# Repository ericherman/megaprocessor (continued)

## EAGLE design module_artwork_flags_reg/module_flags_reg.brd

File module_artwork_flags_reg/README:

Status Register

The status register is a collection of bits that record various aspects
of the results of previous calculations. Whilst PS is internally a 16
bit register only 8 bit are visible to the user, the other hidden 8 bits
are used during complex operations such as multiplication etc. and do
not convey any information from one instruction to the next.

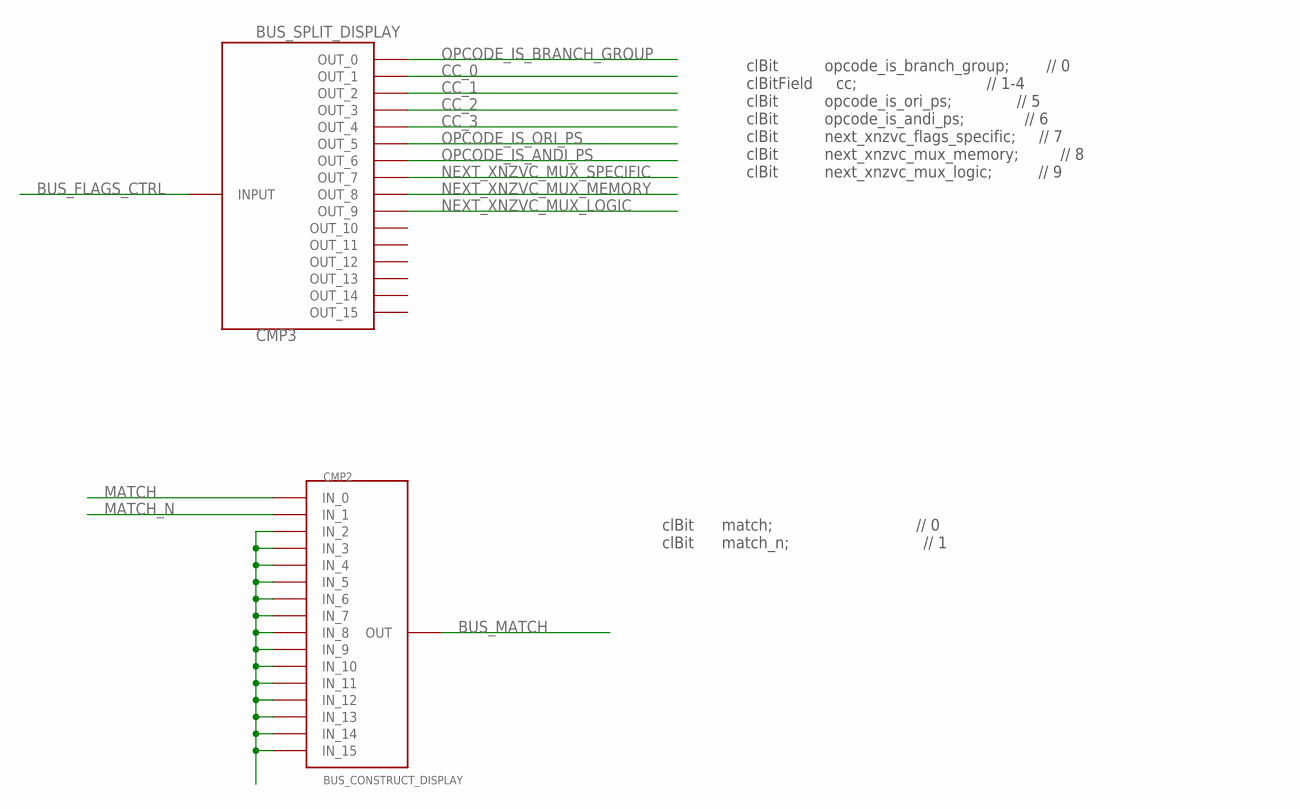
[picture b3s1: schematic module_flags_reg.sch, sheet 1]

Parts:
CMP2: BUS_CONSTRUCT_DISPLAY; BUS_SPLIT_DISPLAY
CMP3: BUS_SPLIT_DISPLAY

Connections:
BUS_FLAGS_CTRL: CMP3.INPUT
BUS_MATCH: CMP2.INPUT (OUT)
CC_0: CMP3.P$2 (OUT_1); also elsewhere on the board
CC_1: CMP3.P$3 (OUT_2); also elsewhere on the board
CC_2: CMP3.P$4 (OUT_3); also elsewhere on the board
CC_3: CMP3.P$5 (OUT_4); also elsewhere on the board
MATCH: CMP2.P$1 (IN_0); also elsewhere on the board
MATCH_N: CMP2.P$2 (IN_1); also elsewhere on the board
unnamed: CMP2.P$3 (IN_2), CMP2.P$4 (IN_3), CMP2.P$5 (IN_4), CMP2.P$6 (IN_5), CMP2.P$7 (IN_6), CMP2.P$8 (IN_7), CMP2.P$9 (IN_8), CMP2.P$10 (IN_9), CMP2.P$11 (IN_10), CMP2.P$12 (IN_11), CMP2.P$13 (IN_12), CMP2.P$14 (IN_13), CMP2.P$15 (IN_14), CMP2.P$16 (IN_15)
NEXT_XNZVC_MUX_LOGIC: CMP3.P$10 (OUT_9); also elsewhere on the board
NEXT_XNZVC_MUX_MEMORY: CMP3.P$9 (OUT_8); also elsewhere on the board
NEXT_XNZVC_MUX_SPECIFIC: CMP3.P$8 (OUT_7); also elsewhere on the board
OPCODE_IS_ANDI_PS: CMP3.P$7 (OUT_6); also elsewhere on the board
OPCODE_IS_BRANCH_GROUP: CMP3.P$1 (OUT_0); also elsewhere on the board
OPCODE_IS_ORI_PS: CMP3.P$6 (OUT_5); also elsewhere on the board

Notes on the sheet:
clBit opcode_is_branch_group; // 0 clBitField cc; // 1-4 clBit opcode_is_ori_ps; // 5 clBit opcode_is_andi_ps; // 6 clBit next_xnzvc_flags_specific; // 7 clBit next_xnzvc_mux_memory; // 8 clBit next_xnzvc_mux_logic; // 9
clBit match; // 0 clBit match_n; // 1

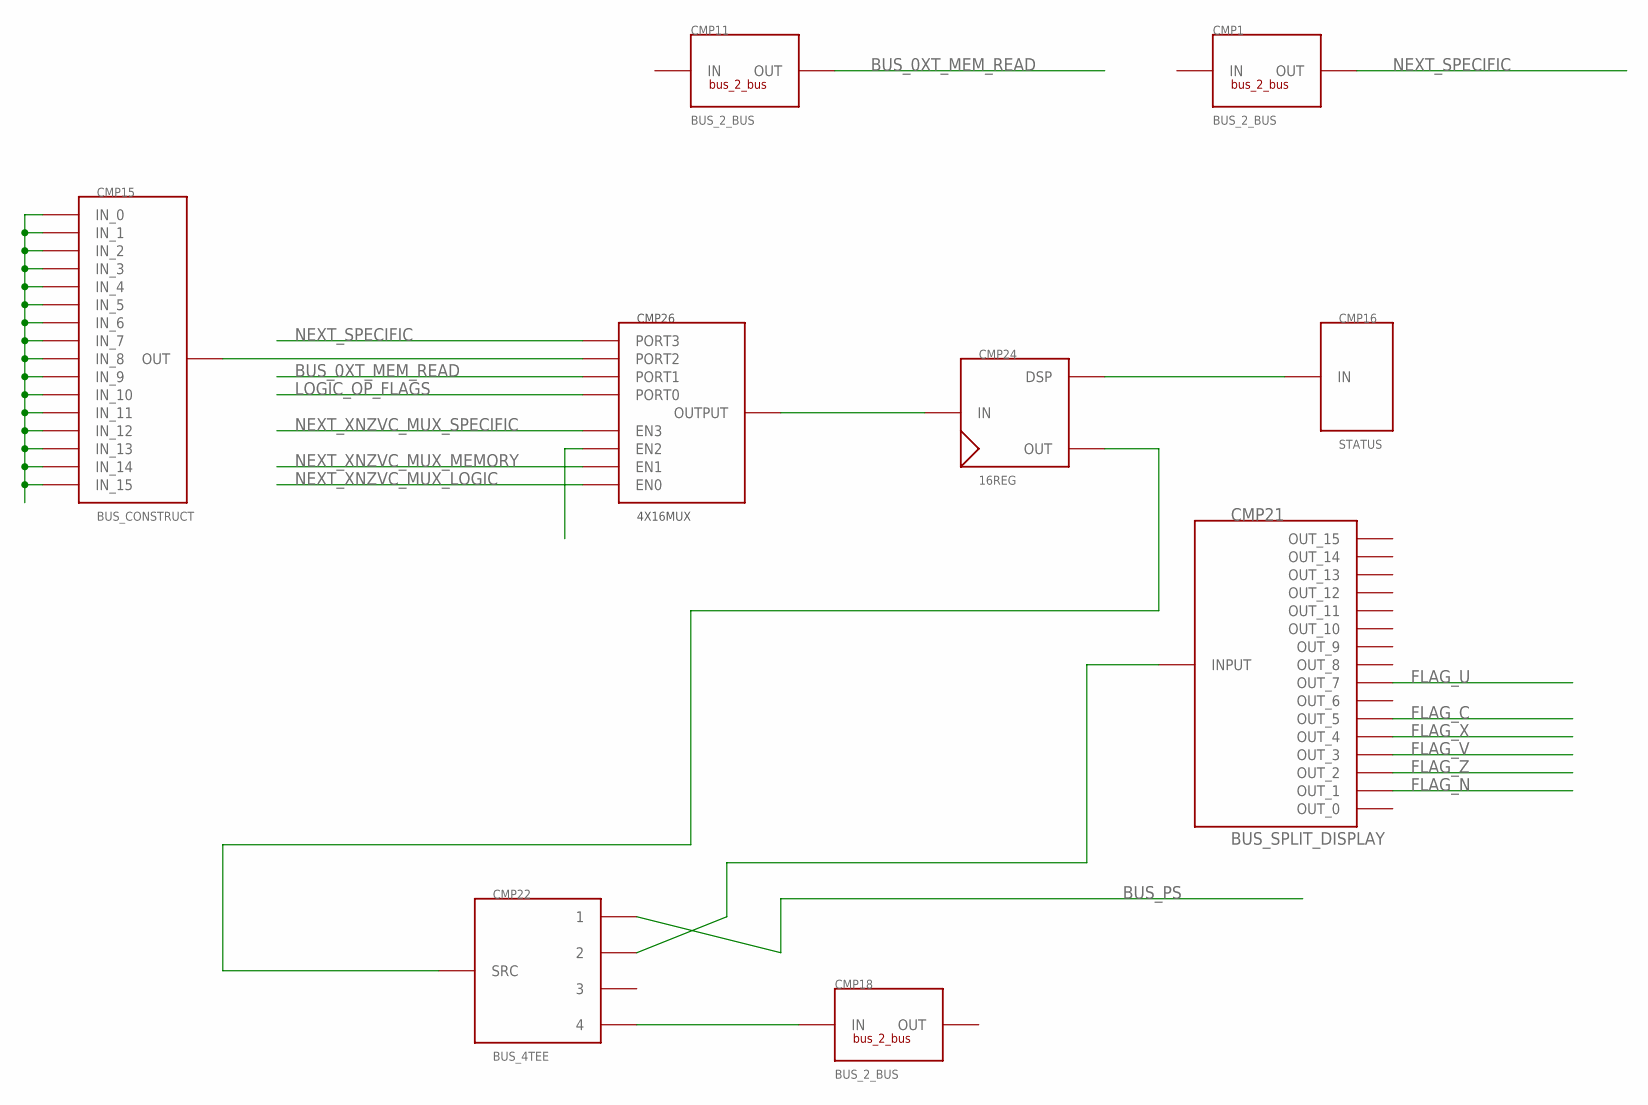
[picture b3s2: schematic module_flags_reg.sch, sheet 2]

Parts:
CMP1, CMP11, CMP18: BUS_2_BUS; BUS2BUS
CMP15: BUS_CONSTRUCT; BUS_SPLIT
CMP16: STATUS
CMP21: BUS_SPLIT_DISPLAY
CMP22: BUS_4TEE
CMP24: 16REG
CMP26: 4X16MUX

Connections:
BUS_0XT_MEM_READ: CMP11.P$2 (OUT), CMP26.PORT1
BUS_PS: CMP22.1; also elsewhere on the board
FLAG_C: CMP21.P$6 (OUT_5); also elsewhere on the board
FLAG_N: CMP21.P$2 (OUT_1); also elsewhere on the board
FLAG_U: CMP21.P$8 (OUT_7); also elsewhere on the board
FLAG_V: CMP21.P$4 (OUT_3); also elsewhere on the board
FLAG_X: CMP21.P$5 (OUT_4)
FLAG_Z: CMP21.P$3 (OUT_2); also elsewhere on the board
LOGIC_OP_FLAGS: CMP26.PORT0; also elsewhere on the board
unnamed: CMP16.P$1, CMP24.DISPLAY (DSP)
unnamed: CMP22.SRC, CMP24.OUT
unnamed: CMP18.P$1 (IN), CMP22.4
unnamed: CMP15.INPUT (OUT), CMP26.PORT2
unnamed: CMP24.INPUT (IN), CMP26.PORTOUT (OUTPUT)
unnamed: CMP15.P$1 (IN_0), CMP15.P$2 (IN_1), CMP15.P$3 (IN_2), CMP15.P$4 (IN_3), CMP15.P$5 (IN_4), CMP15.P$6 (IN_5), CMP15.P$7 (IN_6), CMP15.P$8 (IN_7), CMP15.P$9 (IN_8), CMP15.P$10 (IN_9), CMP15.P$11 (IN_10), CMP15.P$12 (IN_11), CMP15.P$13 (IN_12), CMP15.P$14 (IN_13), CMP15.P$15 (IN_14), CMP15.P$16 (IN_15)
unnamed: CMP21.INPUT, CMP22.2
NEXT_SPECIFIC: CMP1.P$2 (OUT), CMP26.PORT3
NEXT_XNZVC_MUX_LOGIC: CMP26.EN0; also elsewhere on the board
NEXT_XNZVC_MUX_MEMORY: CMP26.EN1; also elsewhere on the board
NEXT_XNZVC_MUX_SPECIFIC: CMP26.EN3; also elsewhere on the board

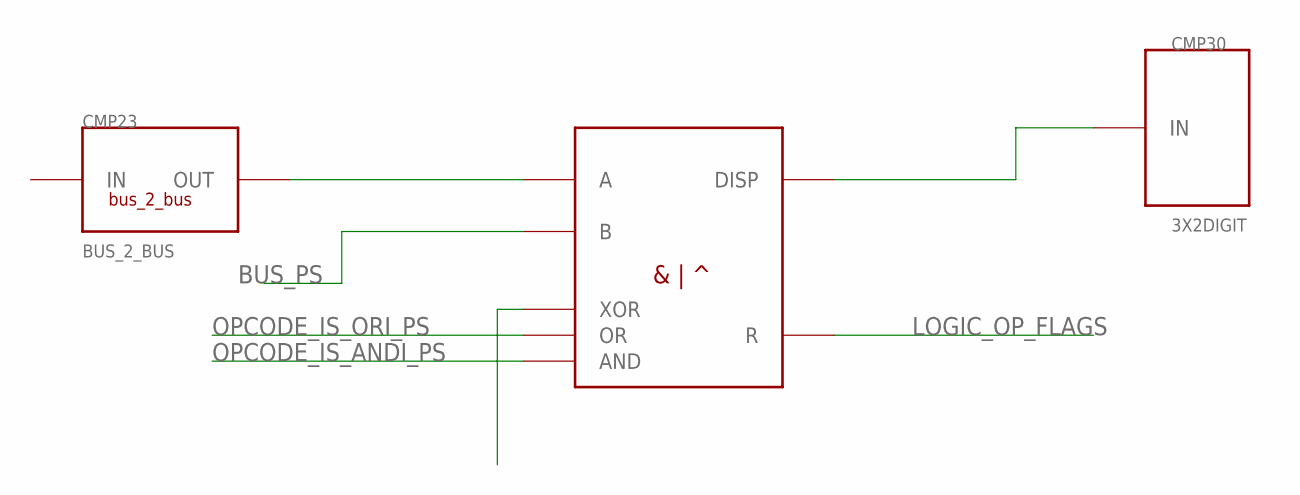
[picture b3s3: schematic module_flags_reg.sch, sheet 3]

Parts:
CMP23: BUS_2_BUS; BUS2BUS
CMP28: 8BIT_LOGIC
CMP30: 3X2DIGIT

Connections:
BUS_PS: CMP28.B; also elsewhere on the board
LOGIC_OP_FLAGS: CMP28.R; also elsewhere on the board
unnamed: CMP28.DISP, CMP30.P$1
unnamed: CMP23.P$2 (OUT), CMP28.A
OPCODE_IS_ANDI_PS: CMP28.AND; also elsewhere on the board
OPCODE_IS_ORI_PS: CMP28.OR; also elsewhere on the board

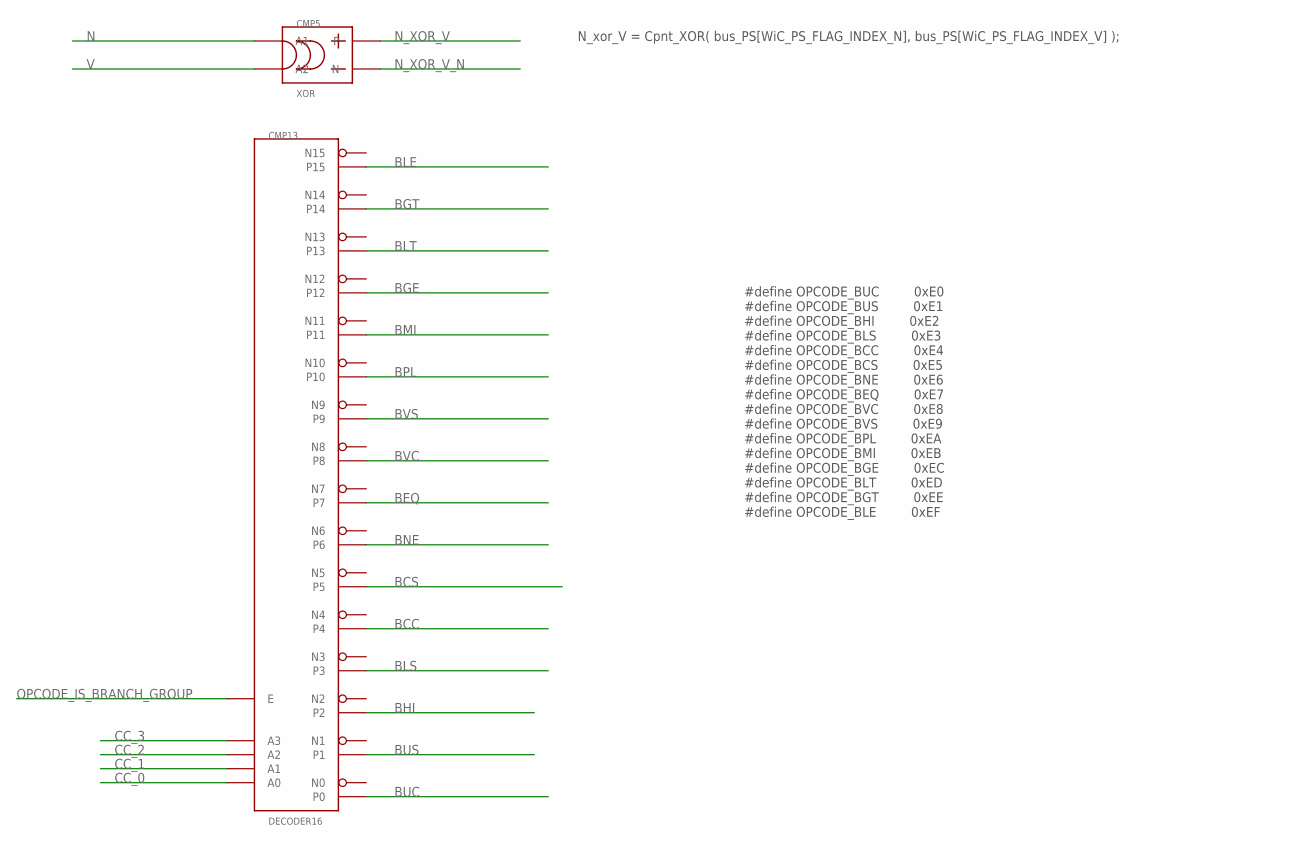
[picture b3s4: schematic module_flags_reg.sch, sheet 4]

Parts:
CMP5: XOR
CMP13: DECODER16

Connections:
BCC: CMP13.P4; also elsewhere on the board
BCS: CMP13.P5; also elsewhere on the board
BEQ: CMP13.P7; also elsewhere on the board
BGE: CMP13.P12; also elsewhere on the board
BGT: CMP13.P14; also elsewhere on the board
BHI: CMP13.P2; also elsewhere on the board
BLE: CMP13.P15; also elsewhere on the board
BLS: CMP13.P3; also elsewhere on the board
BLT: CMP13.P13; also elsewhere on the board
BMI: CMP13.P11; also elsewhere on the board
BNE: CMP13.P6; also elsewhere on the board
BPL: CMP13.P10; also elsewhere on the board
BUC: CMP13.P0; also elsewhere on the board
BUS: CMP13.P1; also elsewhere on the board
BVC: CMP13.P8; also elsewhere on the board
BVS: CMP13.P9; also elsewhere on the board
CC_0: CMP13.A0; also elsewhere on the board
CC_1: CMP13.A1; also elsewhere on the board
CC_2: CMP13.A2; also elsewhere on the board
CC_3: CMP13.A3; also elsewhere on the board
N: CMP5.P$1 (A1); also elsewhere on the board
N_XOR_V: CMP5.OUT_P; also elsewhere on the board
N_XOR_V_N: CMP5.OUT_N (N); also elsewhere on the board
OPCODE_IS_BRANCH_GROUP: CMP13.E; also elsewhere on the board
V: CMP5.P$2 (A2); also elsewhere on the board

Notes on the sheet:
#define OPCODE_BUC 0xE0 #define OPCODE_BUS 0xE1 #define OPCODE_BHI 0xE2 #define OPCODE_BLS 0xE3 #define OPCODE_BCC 0xE4 #define OPCODE_BCS 0xE5 #define OPCODE_BNE 0xE6 #define OPCODE_BEQ 0xE7 #define OPCODE_BVC 0xE8 #define OPCODE_BVS 0xE9 #define OPCODE_BPL 0xEA #define OPCODE_BMI 0xEB #define OPC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
N_xor_V = Cpnt_XOR( bus_PS[WiC_PS_FLAG_INDEX_N], bus_PS[WiC_PS_FLAG_INDEX_V] );

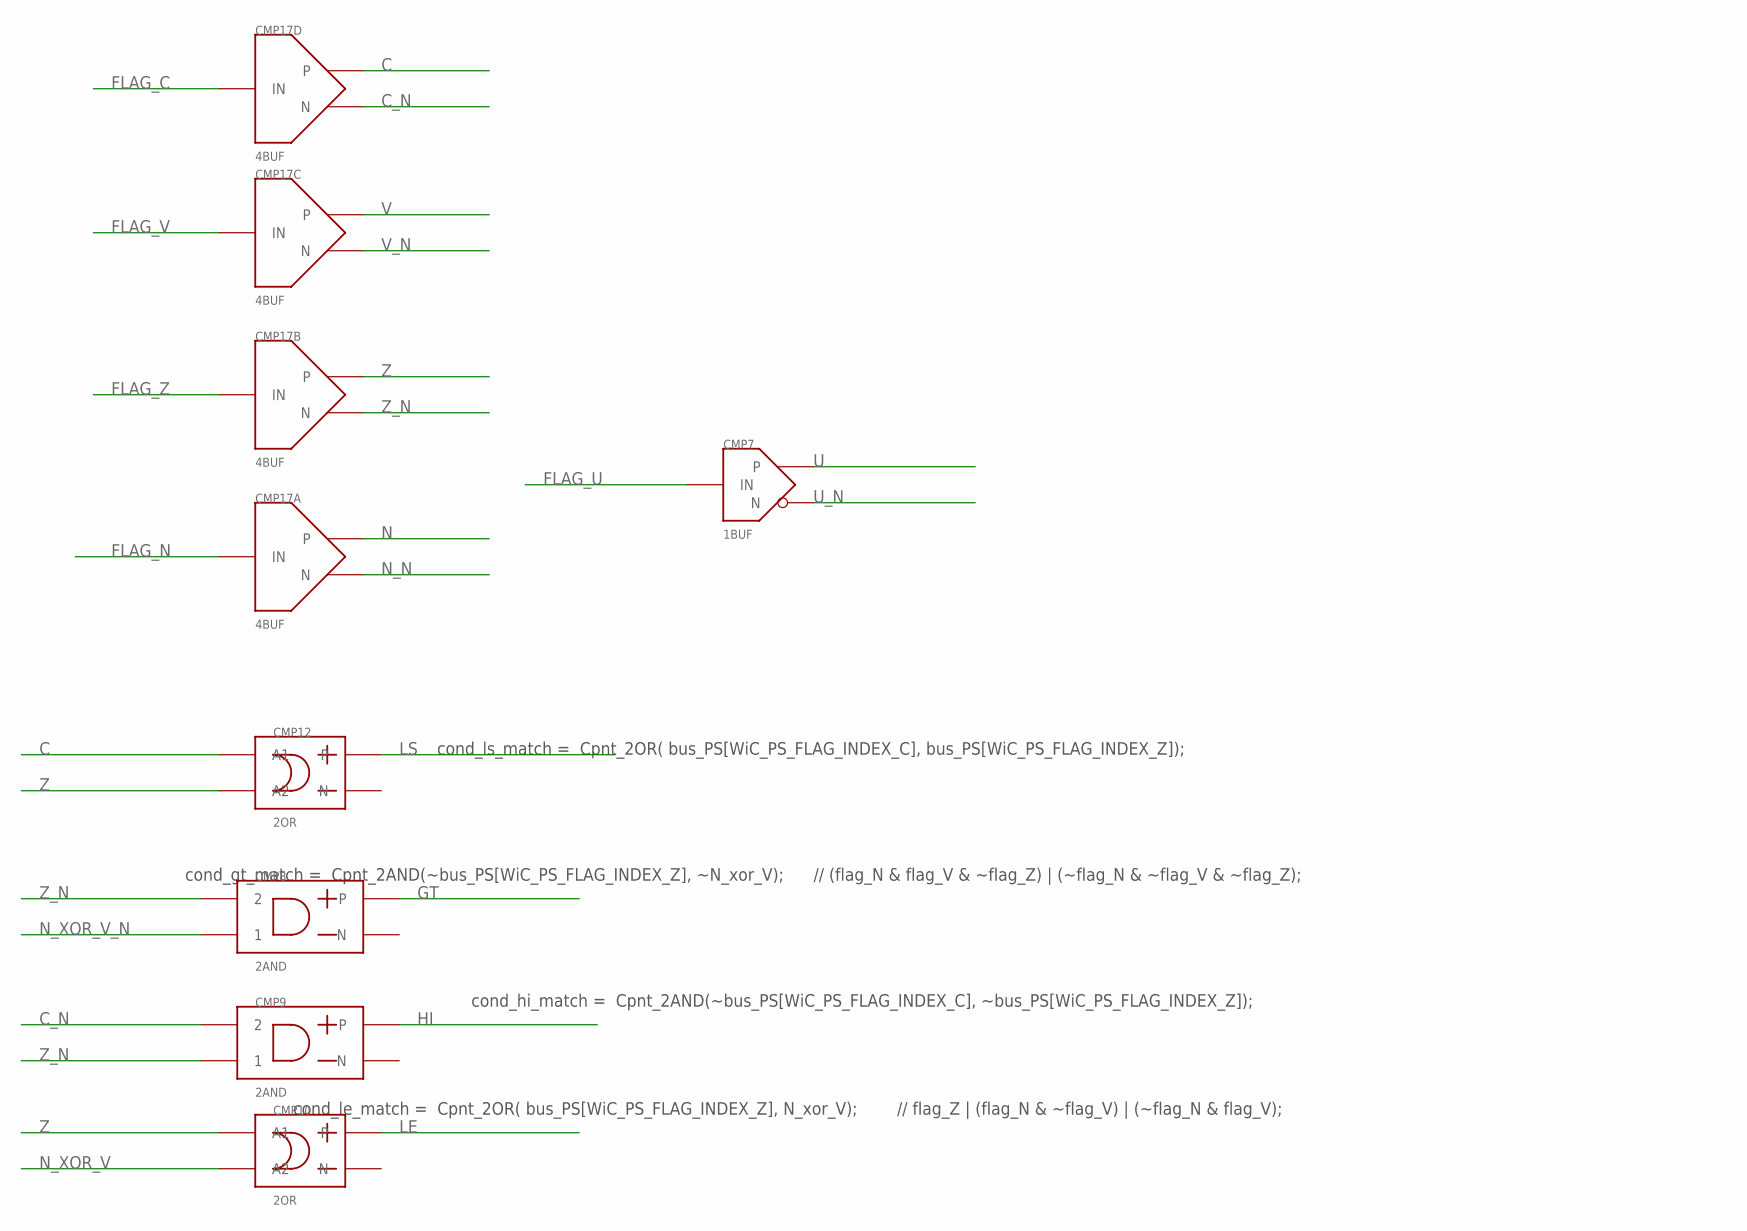
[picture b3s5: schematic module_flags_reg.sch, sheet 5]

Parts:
CMP7: 1BUF
CMP8, CMP9: 2AND
CMP10, CMP12: 2OR
CMP17: 4BUF

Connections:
C: CMP12.P$2 (A1), CMP17.P4; also elsewhere on the board
C_N: CMP9.P$2 (2), CMP17.N4 (N); also elsewhere on the board
FLAG_C: CMP17.A4 (IN); also elsewhere on the board
FLAG_N: CMP17.A1 (IN); also elsewhere on the board
FLAG_U: CMP7.IN; also elsewhere on the board
FLAG_V: CMP17.A3 (IN); also elsewhere on the board
FLAG_Z: CMP17.A2 (IN); also elsewhere on the board
GT: CMP8.OUT_P; also elsewhere on the board
HI: CMP9.OUT_P; also elsewhere on the board
LE: CMP10.OUT_P; also elsewhere on the board
LS: CMP12.OUT_P; also elsewhere on the board
N: CMP17.P1; also elsewhere on the board
N_N: CMP17.N1 (N); also elsewhere on the board
N_XOR_V: CMP10.P$1 (A2); also elsewhere on the board
N_XOR_V_N: CMP8.P$1 (1); also elsewhere on the board
U: CMP7.P; also elsewhere on the board
U_N: CMP7.N; also elsewhere on the board
V: CMP17.P3; also elsewhere on the board
V_N: CMP17.N3 (N); also elsewhere on the board
Z: CMP10.P$2 (A1), CMP12.P$1 (A2), CMP17.P2; also elsewhere on the board
Z_N: CMP8.P$2 (2), CMP9.P$1 (1), CMP17.N2 (N); also elsewhere on the board

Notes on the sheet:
cond_ls_match = Cpnt_2OR( bus_PS[WiC_PS_FLAG_INDEX_C], bus_PS[WiC_PS_FLAG_INDEX_Z]);
cond_gt_match = Cpnt_2AND(~bus_PS[WiC_PS_FLAG_INDEX_Z], ~N_xor_V); // (flag_N & flag_V & ~flag_Z) | (~flag_N & ~flag_V & ~flag_Z);
cond_hi_match = Cpnt_2AND(~bus_PS[WiC_PS_FLAG_INDEX_C], ~bus_PS[WiC_PS_FLAG_INDEX_Z]);
cond_le_match = Cpnt_2OR( bus_PS[WiC_PS_FLAG_INDEX_Z], N_xor_V); // flag_Z | (flag_N & ~flag_V) | (~flag_N & flag_V);

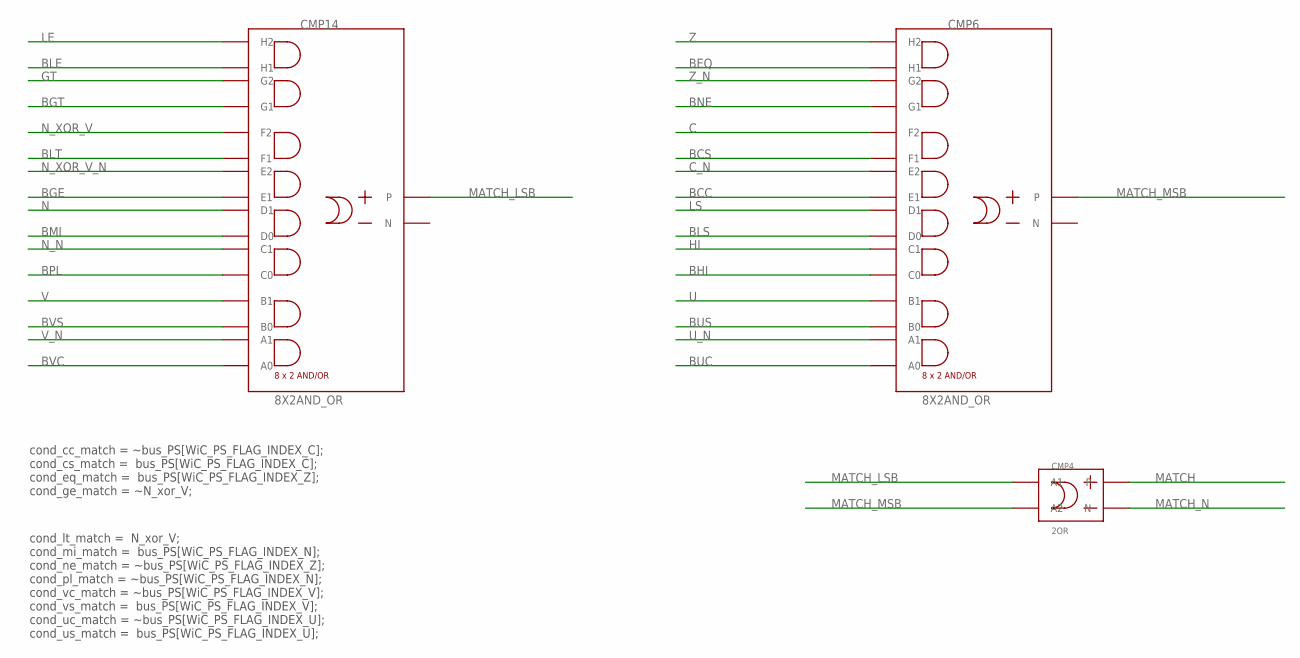
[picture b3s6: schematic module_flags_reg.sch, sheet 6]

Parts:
CMP4: 2OR
CMP6, CMP14: 8X2AND_OR

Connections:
BCC: CMP6.P$9 (E1); also elsewhere on the board
BCS: CMP6.P$11 (F1); also elsewhere on the board
BEQ: CMP6.P$15 (H1); also elsewhere on the board
BGE: CMP14.P$9 (E1); also elsewhere on the board
BGT: CMP14.P$13 (G1); also elsewhere on the board
BHI: CMP6.P$5 (C0); also elsewhere on the board
BLE: CMP14.P$15 (H1); also elsewhere on the board
BLS: CMP6.P$7 (D0); also elsewhere on the board
BLT: CMP14.P$11 (F1); also elsewhere on the board
BMI: CMP14.P$7 (D0); also elsewhere on the board
BNE: CMP6.P$13 (G1); also elsewhere on the board
BPL: CMP14.P$5 (C0); also elsewhere on the board
BUC: CMP6.P$1 (A0); also elsewhere on the board
BUS: CMP6.P$3 (B0); also elsewhere on the board
BVC: CMP14.P$1 (A0); also elsewhere on the board
BVS: CMP14.P$3 (B0); also elsewhere on the board
C: CMP6.P$12 (F2); also elsewhere on the board
C_N: CMP6.P$10 (E2); also elsewhere on the board
GT: CMP14.P$14 (G2); also elsewhere on the board
HI: CMP6.P$6 (C1); also elsewhere on the board
LE: CMP14.P$16 (H2); also elsewhere on the board
LS: CMP6.P$8 (D1); also elsewhere on the board
MATCH: CMP4.OUT_P; also elsewhere on the board
MATCH_LSB: CMP4.P$2 (A1), CMP14.OUT_P
MATCH_MSB: CMP4.P$1 (A2), CMP6.OUT_P
MATCH_N: CMP4.OUT_M (N); also elsewhere on the board
N: CMP14.P$8 (D1); also elsewhere on the board
N_N: CMP14.P$6 (C1); also elsewhere on the board
N_XOR_V: CMP14.P$12 (F2); also elsewhere on the board
N_XOR_V_N: CMP14.P$10 (E2); also elsewhere on the board
U: CMP6.P$4 (B1); also elsewhere on the board
U_N: CMP6.P$2 (A1); also elsewhere on the board
V: CMP14.P$4 (B1); also elsewhere on the board
V_N: CMP14.P$2 (A1); also elsewhere on the board
Z: CMP6.P$16 (H2); also elsewhere on the board
Z_N: CMP6.P$14 (G2); also elsewhere on the board

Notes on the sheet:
cond_cc_match = ~bus_PS[WiC_PS_FLAG_INDEX_C]; cond_cs_match = bus_PS[WiC_PS_FLAG_INDEX_C]; cond_eq_match = bus_PS[WiC_PS_FLAG_INDEX_Z]; cond_ge_match = ~N_xor_V;
cond_lt_match = N_xor_V; cond_mi_match = bus_PS[WiC_PS_FLAG_INDEX_N]; cond_ne_match = ~bus_PS[WiC_PS_FLAG_INDEX_Z]; cond_pl_match = ~bus_PS[WiC_PS_FLAG_INDEX_N]; cond_vc_match = ~bus_PS[WiC_PS_FLAG_INDEX_V]; cond_vs_match = bus_PS[WiC_PS_FLAG_INDEX_V]; cond_uc_match = ~bus_PS[WiC_PS_FLAG_INDEX_U]; 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

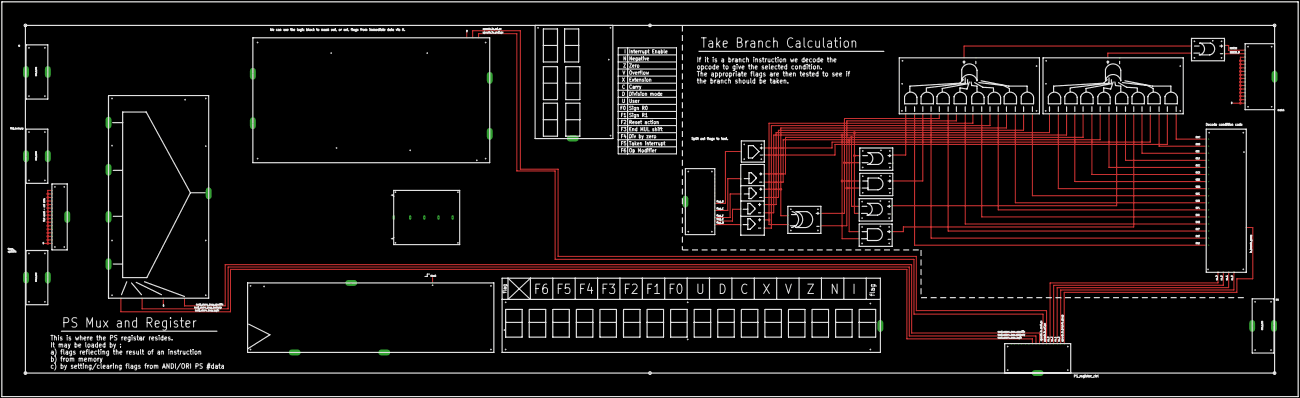
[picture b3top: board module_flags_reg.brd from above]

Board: 2 copper layers, 1397.0 x 425.4 mm, 25 parts (0 on the bottom side), 65 nets.

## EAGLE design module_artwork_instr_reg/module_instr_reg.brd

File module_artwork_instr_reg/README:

Fetch & Instruction

The current instruction is stored here. In addition if the next
instruction has been fetched before it is needed (which usually occurs
during load/store instructions) it is stored here in its own register
(F) till needed. During exception processing the TRAP instruction is
generated here and inserted directly into the instruction register.

Also the read data arrives here and is passed onwards in two forms, zero
extended, and combined with a previously read byte held in H to form a
16 bit value.

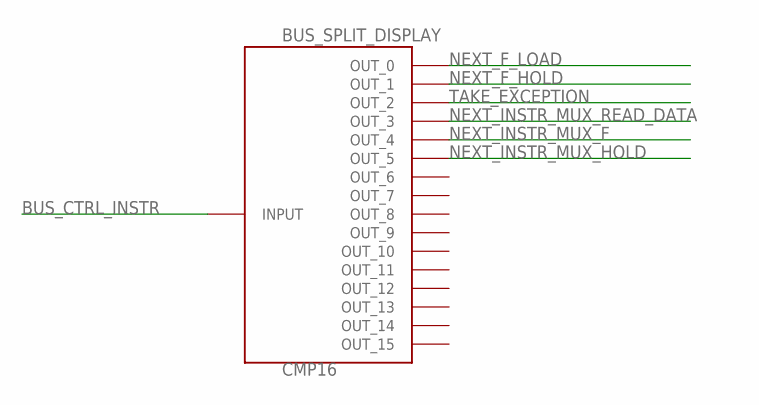
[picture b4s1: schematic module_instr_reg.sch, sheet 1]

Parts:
CMP16: BUS_SPLIT_DISPLAY

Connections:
BUS_CTRL_INSTR: CMP16.INPUT
NEXT_F_HOLD: CMP16.P$2 (OUT_1); also elsewhere on the board
NEXT_F_LOAD: CMP16.P$1 (OUT_0); also elsewhere on the board
NEXT_INSTR_MUX_F: CMP16.P$5 (OUT_4); also elsewhere on the board
NEXT_INSTR_MUX_HOLD: CMP16.P$6 (OUT_5); also elsewhere on the board
NEXT_INSTR_MUX_READ_DATA: CMP16.P$4 (OUT_3); also elsewhere on the board
TAKE_EXCEPTION: CMP16.P$3 (OUT_2); also elsewhere on the board

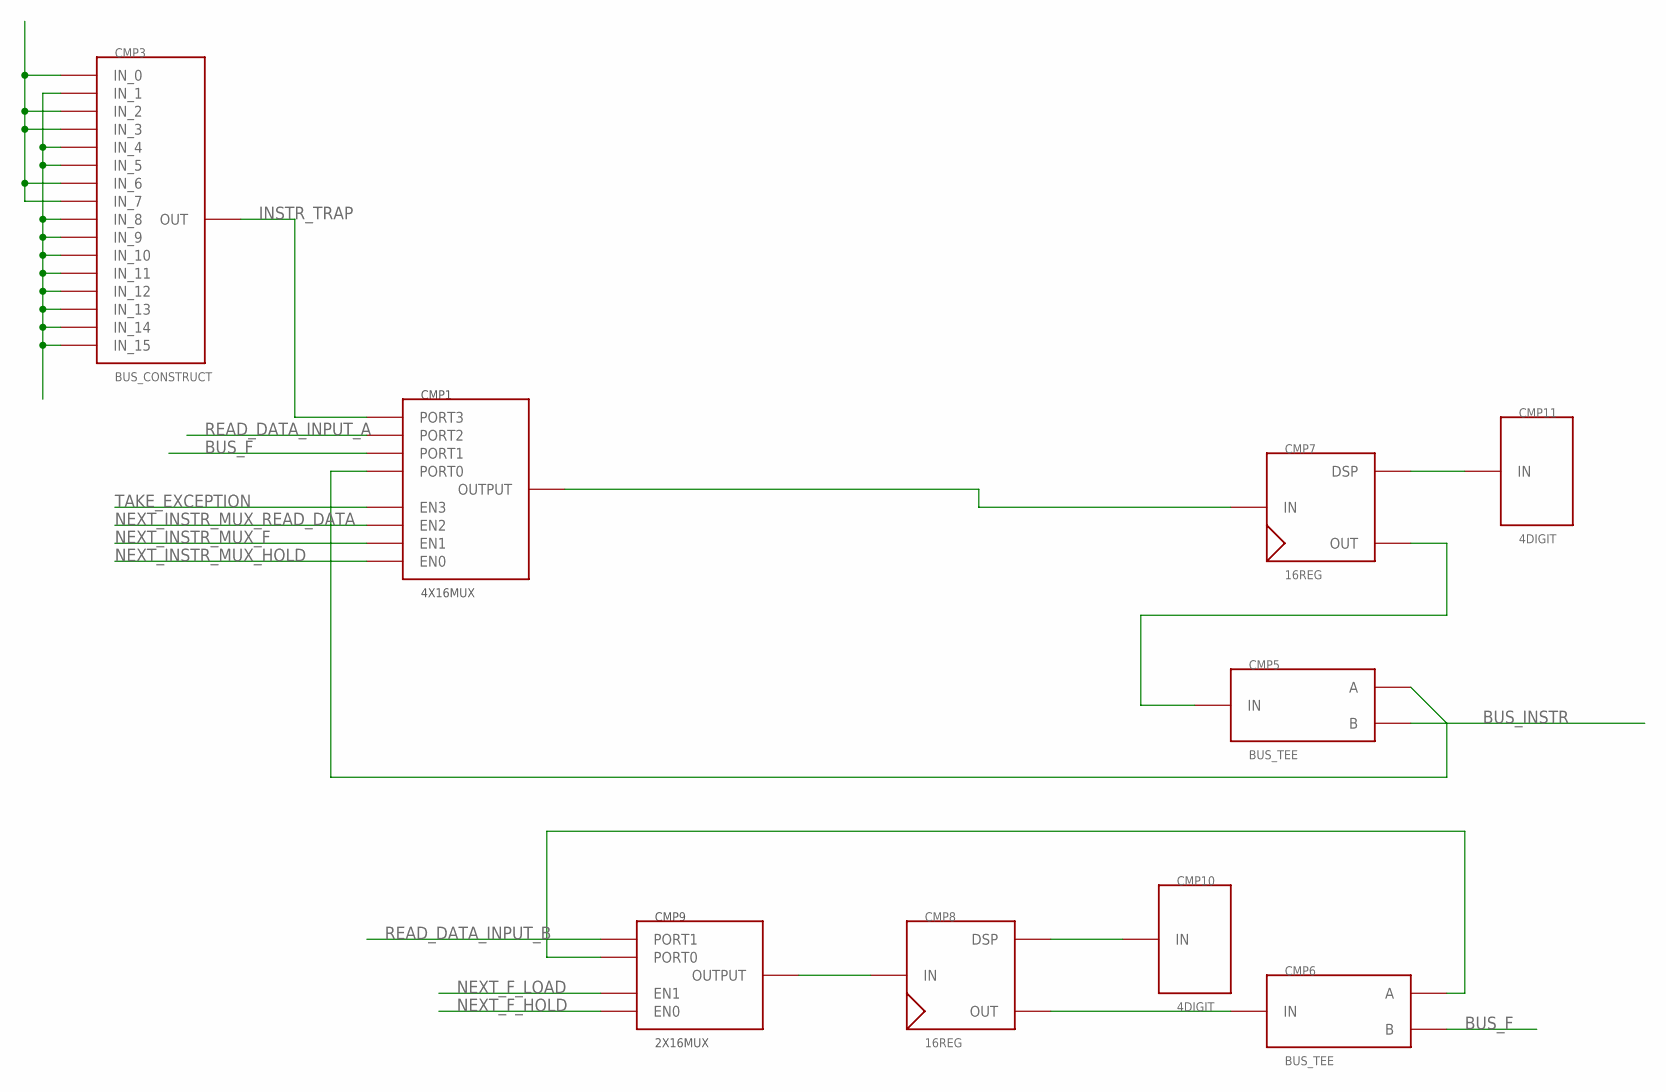
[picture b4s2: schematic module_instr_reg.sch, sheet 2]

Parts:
CMP1: 4X16MUX
CMP3: BUS_CONSTRUCT; BUS_SPLIT
CMP5, CMP6: BUS_TEE
CMP7, CMP8: 16REG
CMP9: 2X16MUX
CMP10, CMP11: 4DIGIT

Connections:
BUS_F: CMP1.PORT1, CMP6.OUTB (B)
BUS_INSTR: CMP5.OUTB (B); also elsewhere on the board
INSTR_TRAP: CMP1.PORT3, CMP3.INPUT (OUT)
unnamed: CMP8.INPUT (IN), CMP9.OUT (OUTPUT)
unnamed: CMP8.DISPLAY (DSP), CMP10.P$1
unnamed: CMP6.OUT_A (A), CMP9.PORT0
unnamed: CMP1.PORTOUT (OUTPUT), CMP7.INPUT (IN)
unnamed: CMP6.INPUT (IN), CMP8.OUT
unnamed: CMP1.PORT0, CMP5.OUT_A (A)
unnamed: CMP7.DISPLAY (DSP), CMP11.P$1
unnamed: CMP5.INPUT (IN), CMP7.OUT
unnamed: CMP3.P$2 (IN_1), CMP3.P$5 (IN_4), CMP3.P$6 (IN_5), CMP3.P$9 (IN_8), CMP3.P$10 (IN_9), CMP3.P$11 (IN_10), CMP3.P$12 (IN_11), CMP3.P$13 (IN_12), CMP3.P$14 (IN_13), CMP3.P$15 (IN_14), CMP3.P$16 (IN_15)
unnamed: CMP3.P$1 (IN_0), CMP3.P$3 (IN_2), CMP3.P$4 (IN_3), CMP3.P$7 (IN_6), CMP3.P$8 (IN_7)
NEXT_F_HOLD: CMP9.EN0; also elsewhere on the board
NEXT_F_LOAD: CMP9.EN1; also elsewhere on the board
NEXT_INSTR_MUX_F: CMP1.EN1; also elsewhere on the board
NEXT_INSTR_MUX_HOLD: CMP1.EN0; also elsewhere on the board
NEXT_INSTR_MUX_READ_DATA: CMP1.EN2; also elsewhere on the board
READ_DATA_INPUT_A: CMP1.PORT2; also elsewhere on the board
READ_DATA_INPUT_B: CMP9.PORT1; also elsewhere on the board
TAKE_EXCEPTION: CMP1.EN3; also elsewhere on the board

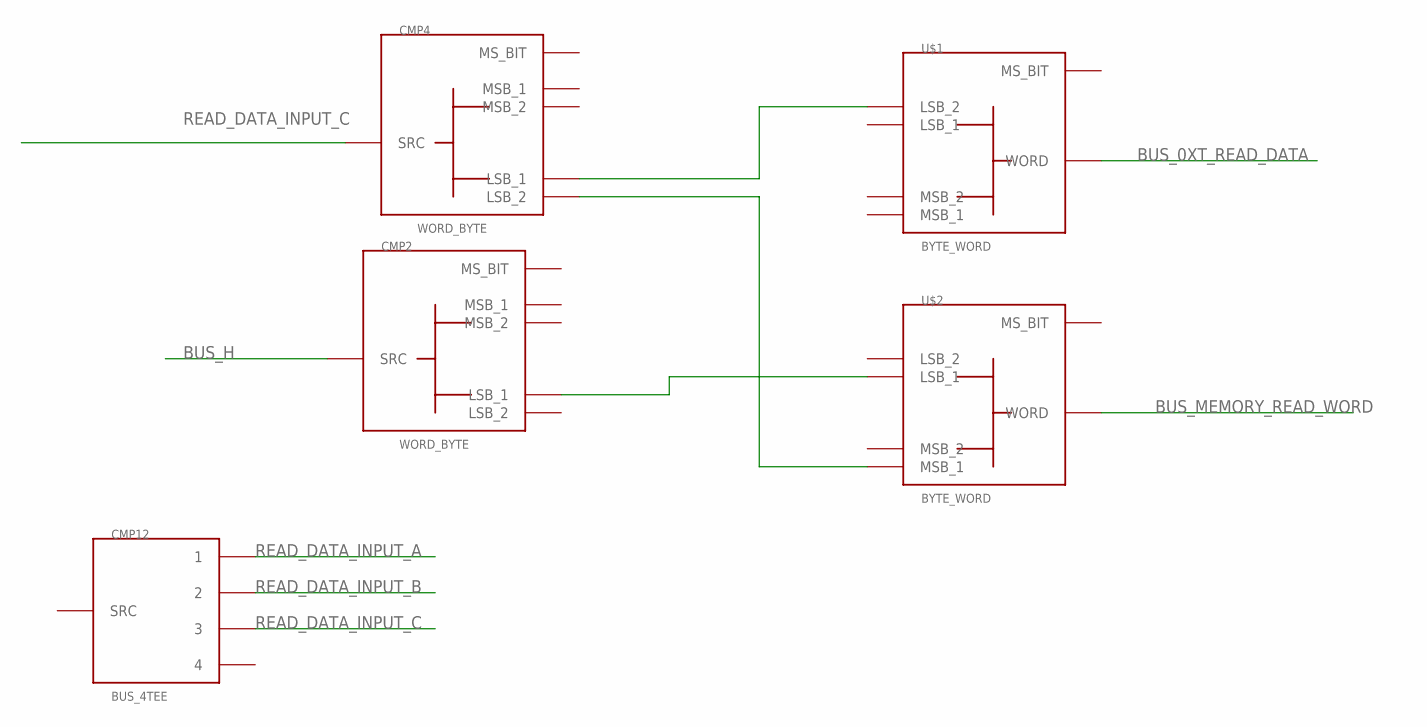
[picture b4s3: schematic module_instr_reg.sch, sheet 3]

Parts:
CMP2, CMP4: WORD_BYTE
CMP12: BUS_4TEE
U$1, U$2: BYTE_WORD; WORD_BYTE

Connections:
BUS_0XT_READ_DATA: U$1.SRC (WORD)
BUS_H: CMP2.SRC
BUS_MEMORY_READ_WORD: U$2.SRC (WORD)
unnamed: CMP2.LSB_1, U$2.LSB_1
unnamed: CMP4.LSB_1, U$1.LSB_2
unnamed: CMP4.LSB_2, U$2.MSB_1
READ_DATA_INPUT_A: CMP12.1; also elsewhere on the board
READ_DATA_INPUT_B: CMP12.2; also elsewhere on the board
READ_DATA_INPUT_C: CMP4.SRC, CMP12.3

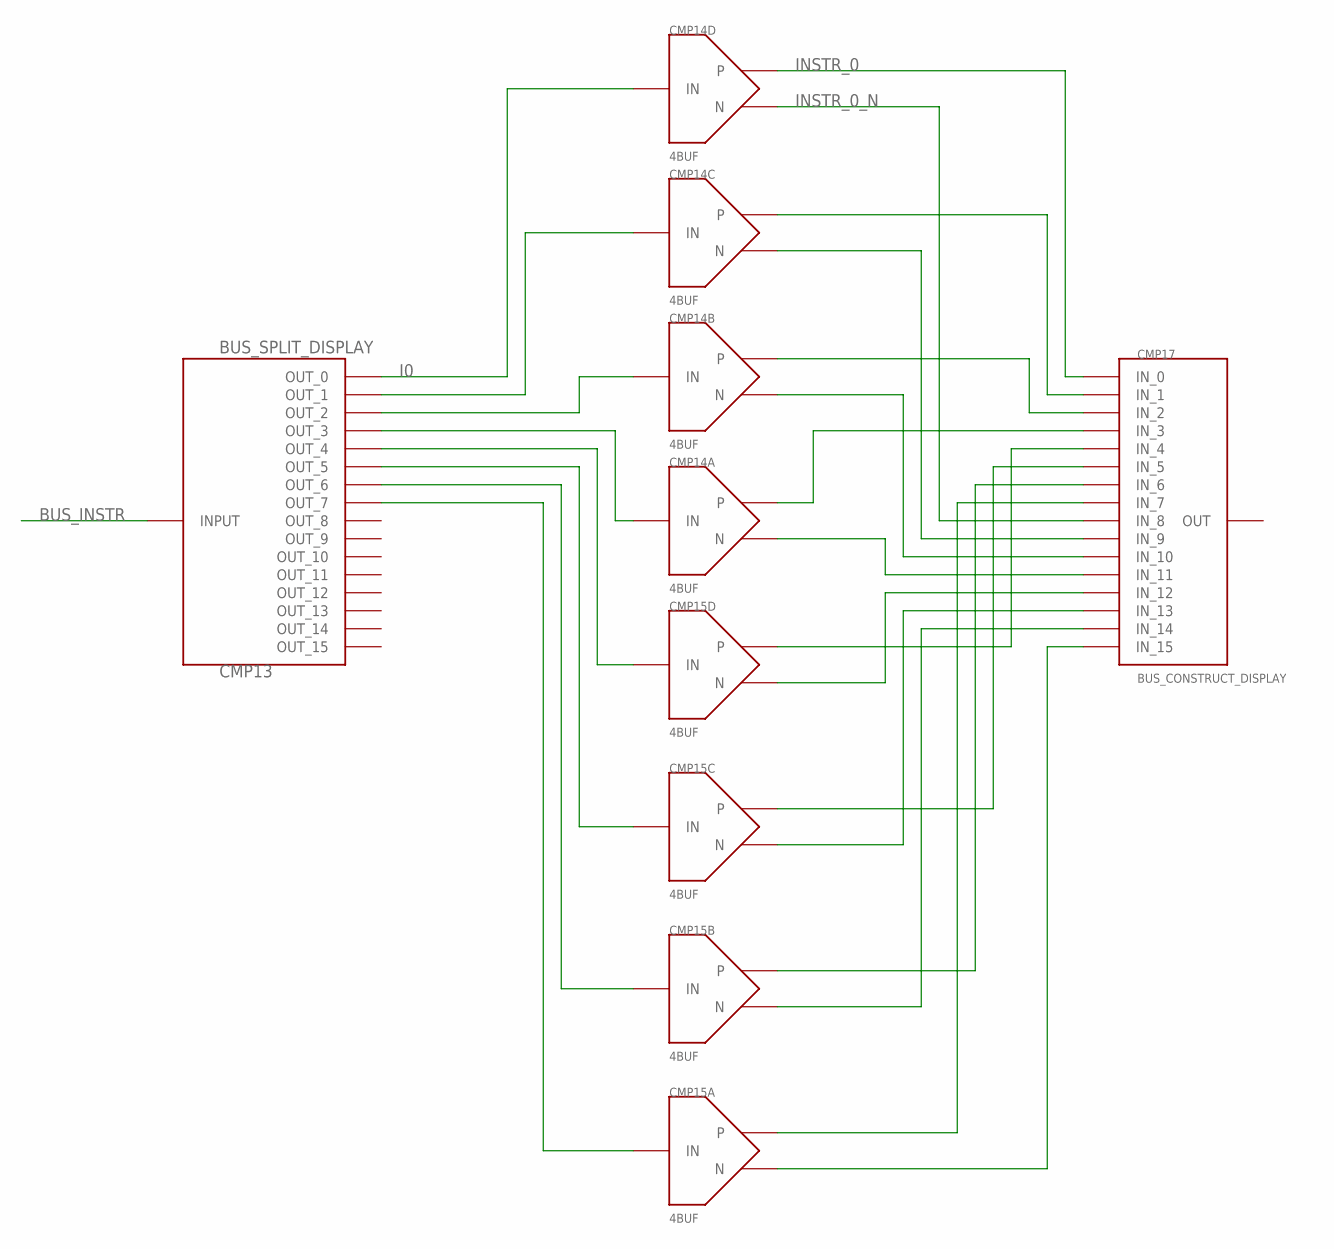
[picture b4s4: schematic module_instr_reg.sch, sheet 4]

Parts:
CMP13: BUS_SPLIT_DISPLAY
CMP14, CMP15: 4BUF
CMP17: BUS_CONSTRUCT_DISPLAY; BUS_SPLIT_DISPLAY

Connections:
BUS_INSTR: CMP13.INPUT; also elsewhere on the board
I0: CMP13.P$1 (OUT_0), CMP14.A4 (IN)
INSTR_0: CMP14.P4, CMP17.P$1 (IN_0)
INSTR_0_N: CMP14.N4 (N), CMP17.P$9 (IN_8)
unnamed: CMP13.P$2 (OUT_1), CMP14.A3 (IN)
unnamed: CMP13.P$3 (OUT_2), CMP14.A2 (IN)
unnamed: CMP13.P$4 (OUT_3), CMP14.A1 (IN)
unnamed: CMP13.P$5 (OUT_4), CMP15.A4 (IN)
unnamed: CMP13.P$6 (OUT_5), CMP15.A3 (IN)
unnamed: CMP13.P$7 (OUT_6), CMP15.A2 (IN)
unnamed: CMP13.P$8 (OUT_7), CMP15.A1 (IN)
unnamed: CMP14.P3, CMP17.P$2 (IN_1)
unnamed: CMP14.P2, CMP17.P$3 (IN_2)
unnamed: CMP14.P1, CMP17.P$4 (IN_3)
unnamed: CMP15.P4, CMP17.P$5 (IN_4)
unnamed: CMP15.P3, CMP17.P$6 (IN_5)
unnamed: CMP15.P2, CMP17.P$7 (IN_6)
unnamed: CMP15.P1, CMP17.P$8 (IN_7)
unnamed: CMP14.N3 (N), CMP17.P$10 (IN_9)
unnamed: CMP14.N2 (N), CMP17.P$11 (IN_10)
unnamed: CMP14.N1 (N), CMP17.P$12 (IN_11)
unnamed: CMP15.N4 (N), CMP17.P$13 (IN_12)
unnamed: CMP15.N3 (N), CMP17.P$14 (IN_13)
unnamed: CMP15.N2 (N), CMP17.P$15 (IN_14)
unnamed: CMP15.N1 (N), CMP17.P$16 (IN_15)

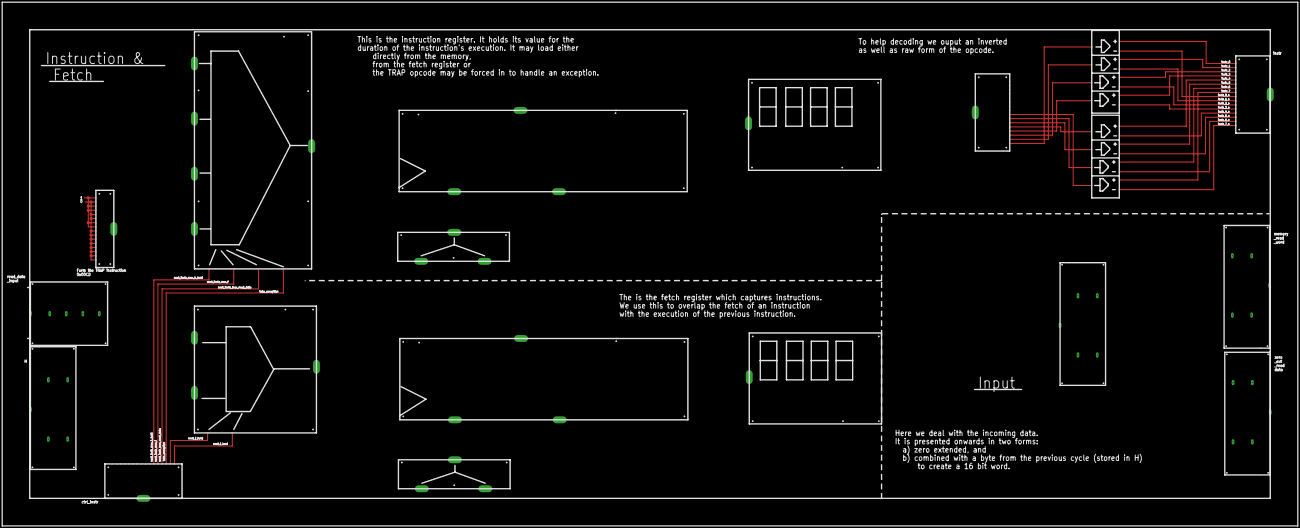
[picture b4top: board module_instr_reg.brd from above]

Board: 2 copper layers, 1193.8 x 482.6 mm, 19 parts (0 on the bottom side), 49 nets.
